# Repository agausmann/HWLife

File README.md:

# HWLife

Experiments in implementing Conway's Game of Life using tiled hardware.

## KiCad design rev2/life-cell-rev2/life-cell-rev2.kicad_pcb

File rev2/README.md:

# (WIP) HWLife Rev2

**This revision is on indefinite hold; I am currently working on a design
with independent modules and no backplane (rev3).**

A redesign of the backplane system.

Major changes:

- Module hardware
  - CH32V003
  - Right-angle backplane connectors and LEDs (allowing single-sided SMT assembly)
  - RGB LEDs (WS2812)

- Comms
  - Analog neighbor communication
  - Serial communication to individual modules (for programming state or dimming)

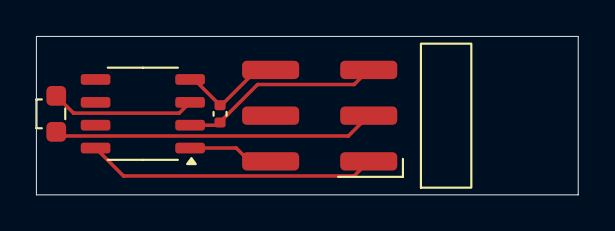
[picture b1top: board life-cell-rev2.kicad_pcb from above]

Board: 2 copper layers, 30.1 x 8.8 mm, 4 parts (0 on the bottom side), 6 nets.

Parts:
C1: 100nF; C_0402_1005Metric
D1: LED; LiteOn_LTST-S270KxKT
J1: Backplane; Conn_HCTL_PZ254-2-03-WS
U1: CH32V003J4M6; SOP-8_3.9x4.9mm_P1.27mm

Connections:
/DIM: D1.1 (K), J1.3
/LED: D1.2 (A), U1.3 (PA2)
/RX: J1.2, U1.1 (PD6/PA1)
/TX/SWIO: J1.1, U1.8 (PD1/PD4/PD5)
VDD: C1.1, J1.6, U1.4 (VDD)
VSS: C1.2, J1.5, U1.2 (VSS)

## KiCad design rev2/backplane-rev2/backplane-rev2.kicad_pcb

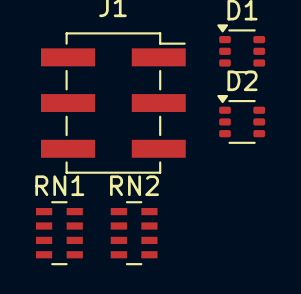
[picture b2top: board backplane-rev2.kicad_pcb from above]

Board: 2 copper layers, 5 parts (0 on the bottom side), 9 nets, no tracks yet.

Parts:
D1, D2: BAT54ADW; SOT-363_SC-70-6
J1: Module; PinSocket_2x03_P2.54mm_Vertical_SMD
RN1, RN2: 10K; R_Array_Concave_4x0603

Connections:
/A1/D: D1.3 (A), D1.6 (A), D2.3 (A), D2.6 (A), J1.3
unnamed: D1.1 (K), RN1.5 (R4.2)
unnamed: D1.2 (K), RN1.6 (R3.2)
unnamed: D1.4 (K), RN1.7 (R2.2)
unnamed: D1.5 (K), RN1.8 (R1.2)
unnamed: D2.1 (K), RN2.5 (R4.2)
unnamed: D2.2 (K), RN2.6 (R3.2)
unnamed: D2.4 (K), RN2.7 (R2.2)
unnamed: D2.5 (K), RN2.8 (R1.2)

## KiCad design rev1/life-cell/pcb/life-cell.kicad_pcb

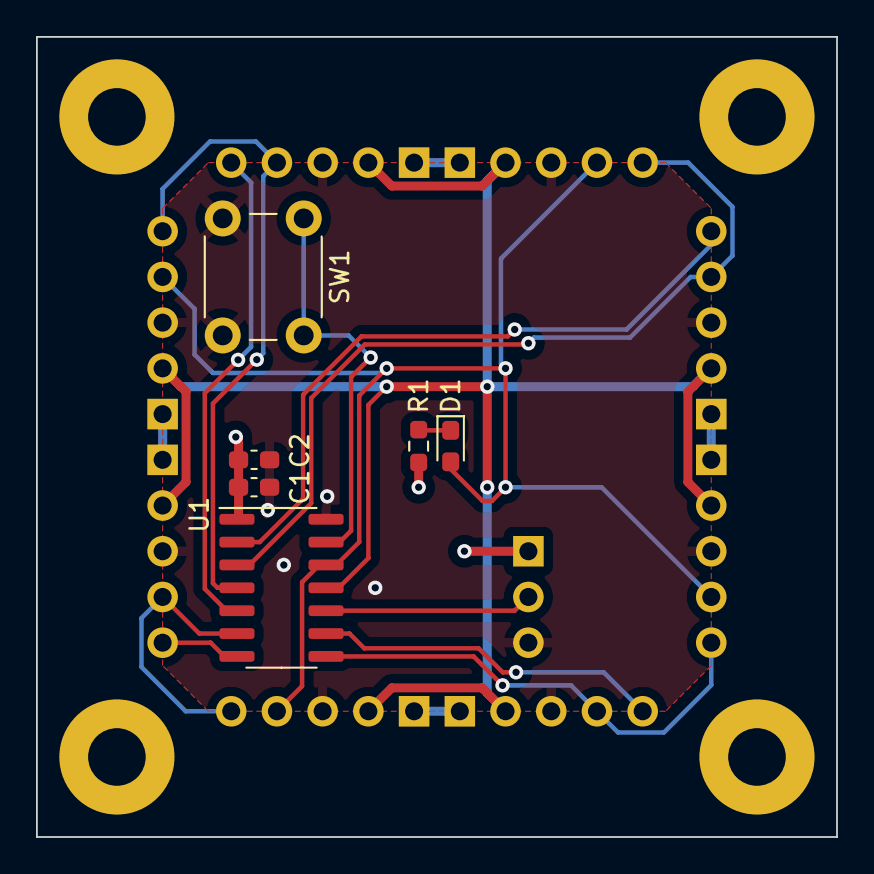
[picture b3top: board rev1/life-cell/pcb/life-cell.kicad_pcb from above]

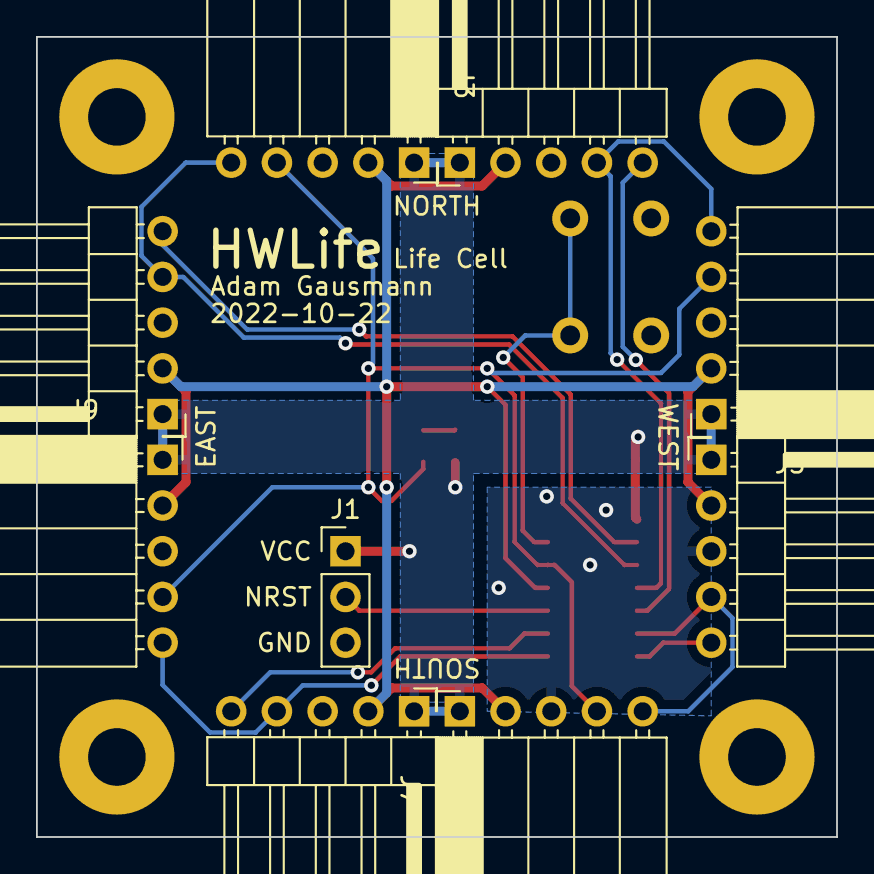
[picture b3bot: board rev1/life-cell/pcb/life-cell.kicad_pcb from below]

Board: 2 copper layers, 44.4 x 44.4 mm, 19 parts (9 on the bottom side), 15 nets.

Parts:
C1: 100nF; C_0603_1608Metric_Pad1.08x0.95mm_HandSolder
C2: Bulk; C_0603_1608Metric_Pad1.08x0.95mm_HandSolder
D1: LED; LED_0603_1608Metric_Pad1.05x0.95mm_HandSolder
H1, H2, H3, H4: M3; MountingHole_3.2mm_M3_Pad
J1: UPDI; PinHeader_1x03_P2.54mm_Vertical
J2, J4, J6, J8: Interconnect In; PinHeader_1x05_P2.54mm_Horizontal
J3, J5, J7, J9: Interconnect Out; PinSocket_1x05_P2.54mm_Horizontal
R1: 120R; R_0603_1608Metric_Pad0.98x0.95mm_HandSolder
SW1: Toggle; SW_PUSH_6mm_H4.3mm
U1: ATtiny404-SS; SOIC-14_3.9x8.7mm_P1.27mm

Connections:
/Cell/ADJ1: J2.4, J5.5, U1.4 (PA6)
/Cell/ADJ2: J3.5, J8.4, U1.3 (PA5)
/Cell/ADJ3: J6.4, J9.5, U1.8 (PB1)
/Cell/ADJ4: J4.4, J7.5, U1.6 (PB3)
/Cell/CLK: J2.2, J3.2, J4.2, J5.2, J6.2, J7.2, J8.2, J9.2, U1.11 (PA1)
/Cell/DIA1: J2.5, U1.5 (PA7)
/Cell/DIA2: J8.5, U1.2 (PA4)
/Cell/DIA3: J6.5, U1.9 (PB0)
/Cell/DIA4: J4.5, U1.7 (PB2)
/Cell/NRST: J1.2, U1.10 (~RESET/PA0)
/Cell/STATE: D1.2 (A), J3.4, J5.4, J7.4, J9.4, U1.12 (PA2)
/Cell/TOGGLE: SW1.1, U1.13 (PA3)
GND: C1.2, C2.2, J1.3, J2.3, J3.3, J4.3, J5.3, J6.3, J7.3, J8.3, J9.3, SW1.2, U1.14 (GND)
unnamed: D1.1 (K), R1.2
VCC: C1.1, C2.1, J1.1, J2.1, J3.1, J4.1, J5.1, J6.1, J7.1, J8.1, J9.1, R1.1, U1.1 (VCC)

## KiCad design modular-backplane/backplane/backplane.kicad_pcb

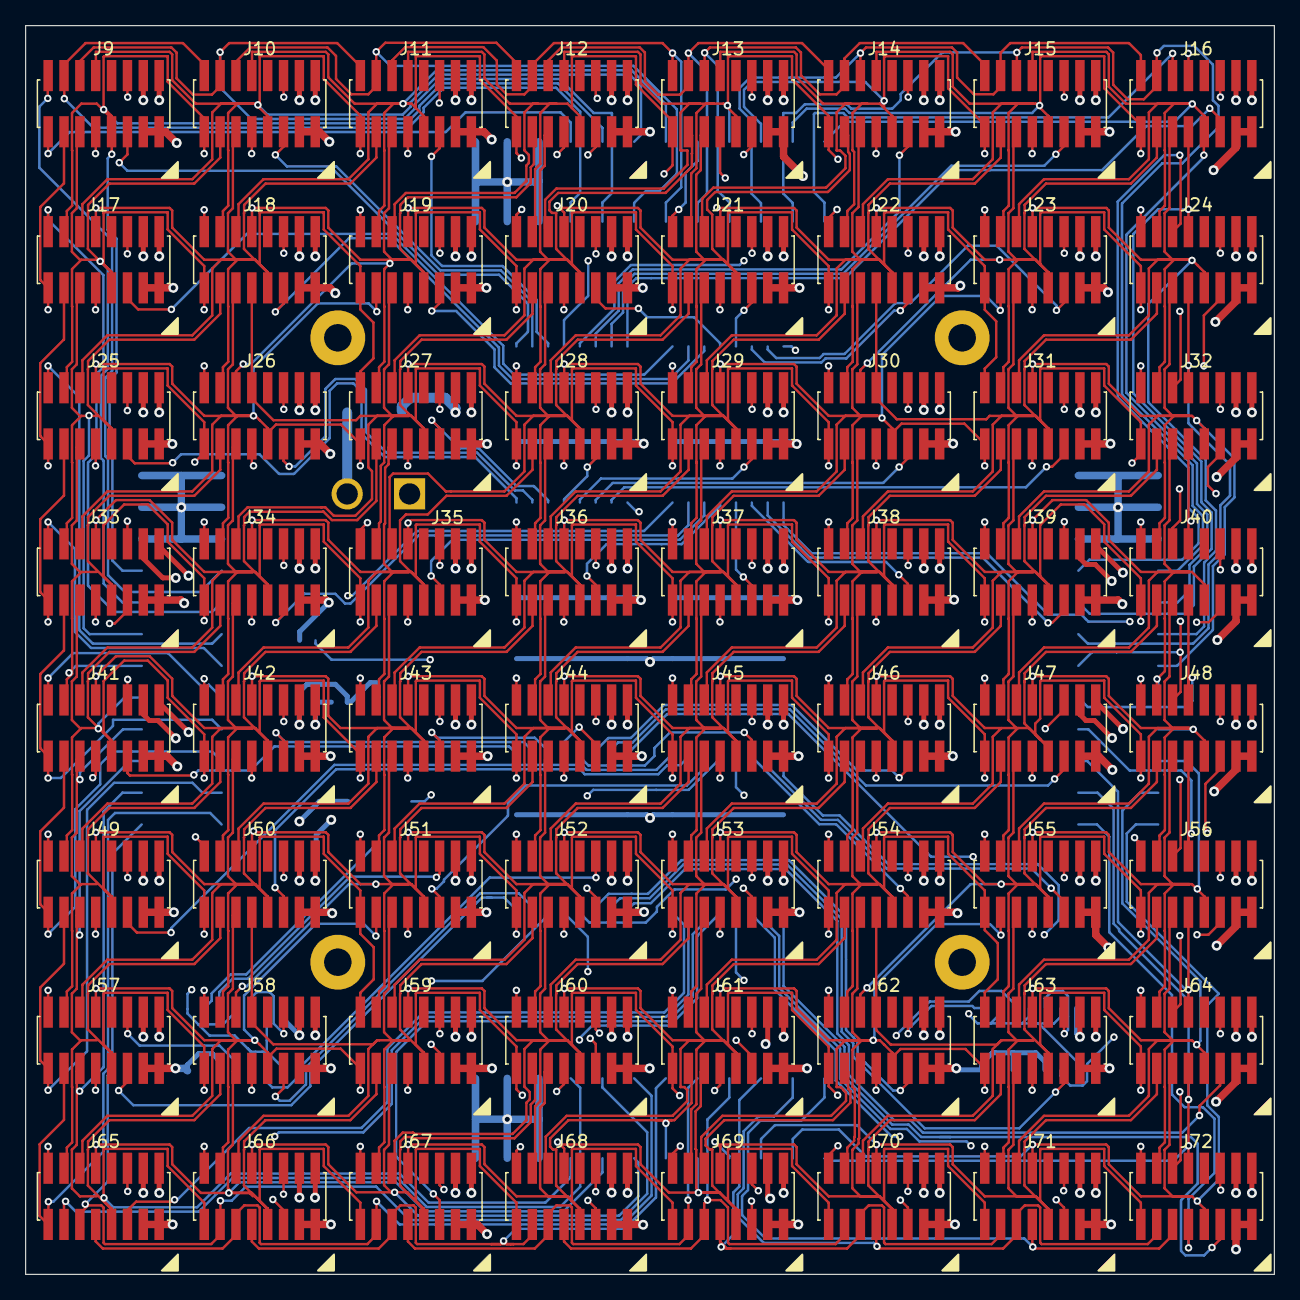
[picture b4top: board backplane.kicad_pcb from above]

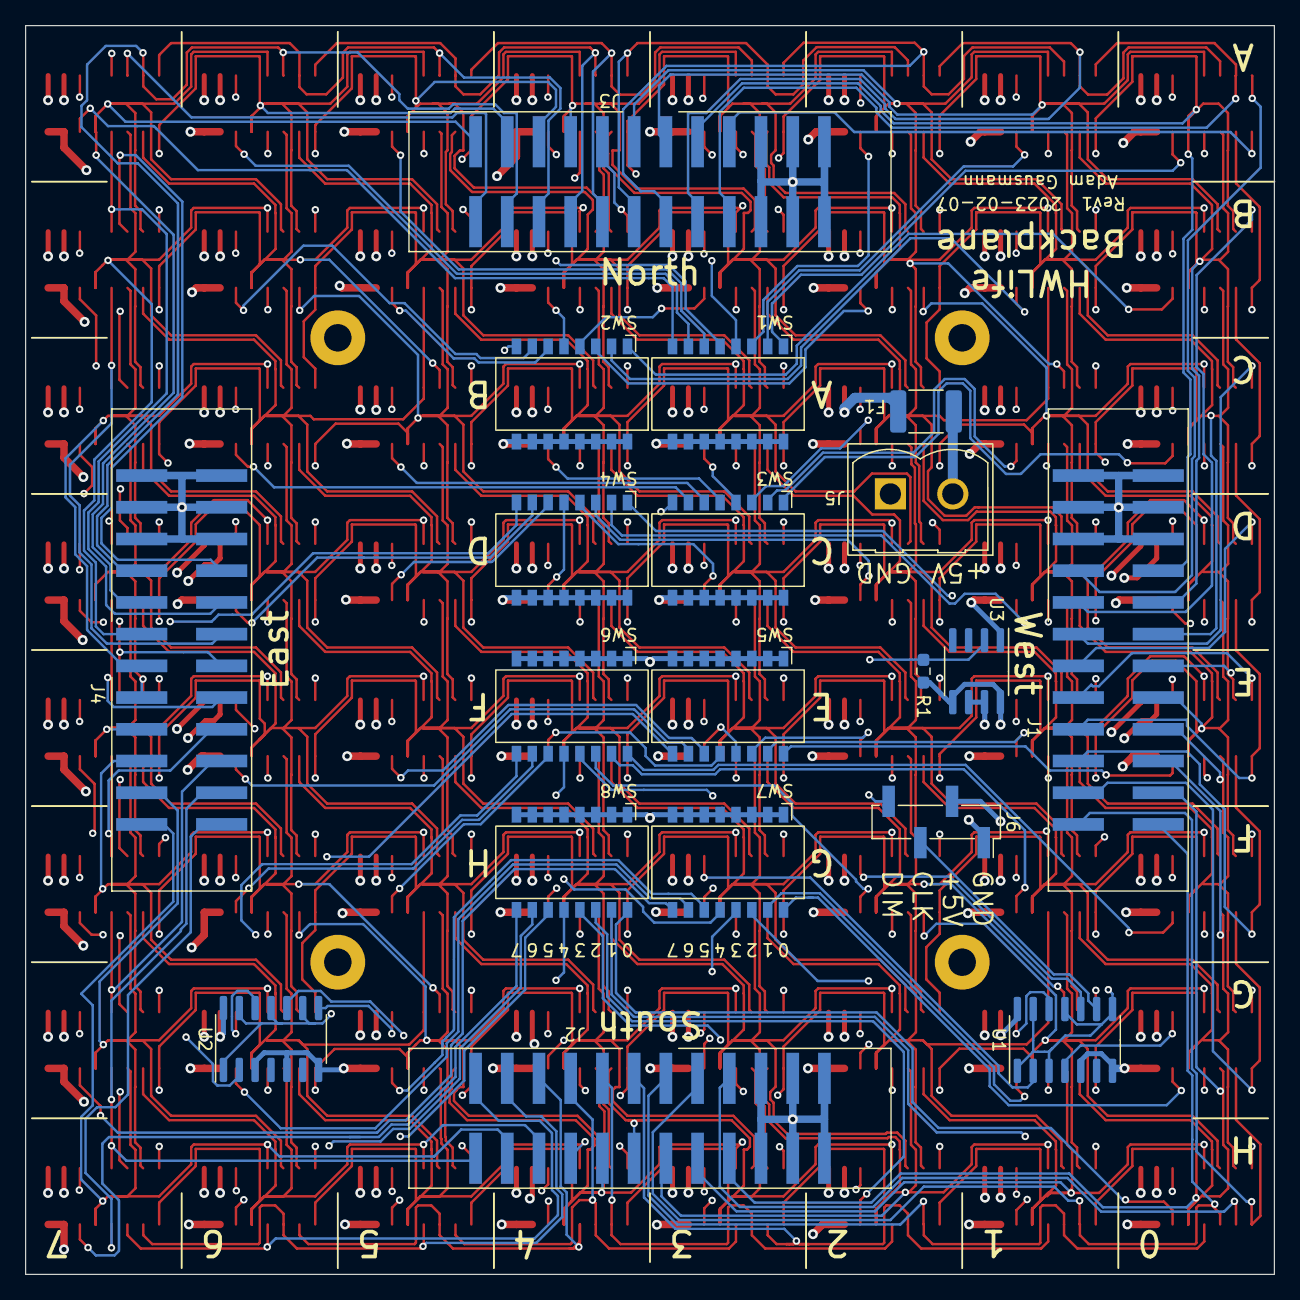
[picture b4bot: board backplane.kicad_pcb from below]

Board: 4 copper layers, 100.0 x 100.0 mm, 87 parts (19 on the bottom side), 179 nets.

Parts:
F1: 6V 3A; Fuse_1812_4532Metric_Pad1.30x3.40mm_HandSolder
H1, H2, H3, H4: MountingHole; MountingHole_2.2mm_M2_Pad
J1: West; JILN_321024M_02x12_P2.54mm_Vertical
J2: South; JILN_321024M_02x12_P2.54mm_Vertical
J3: North; JILN_321024M_02x12_P2.54mm_Vertical
J4: East; JILN_321024M_02x12_P2.54mm_Vertical
J5: 25-E900-02; Conn_NTE_25-E900-02_01x02_P5.00mm_Vertical
J6: MGMT; PinHeader_1x04_P2.54mm_Vertical_SMD_Pin1Right
J9, J10, J11, J12, J13, J14, J15, J16, J17, J18, J19, J20, J21, J22, J23, J24, J25, J26, J27, J28, J29, J30, J31, J32, J33, J34, J35, J36, J37, J38, J39, J40, J41, J42, J43, J44, J45, J46, J47, J48, J49, J50, J51, J52, J53, J54, J55, J56, J57, J58, J59, J60, J61, J62, J63, J64, J65, J66, J67, J68, J69, J70, J71, J72: Module; DEALON_DZ127S-22-16-55_02x08_P1.27mm_Vertical
R1: 10k; R_0603_1608Metric_Pad0.98x0.95mm_HandSolder
SW1: A; SW_DIP_SPSTx08_Slide_DEALON_SP-08P_P1.27mm
SW2: B; SW_DIP_SPSTx08_Slide_DEALON_SP-08P_P1.27mm
SW3: C; SW_DIP_SPSTx08_Slide_DEALON_SP-08P_P1.27mm
SW4: D; SW_DIP_SPSTx08_Slide_DEALON_SP-08P_P1.27mm
SW5: E; SW_DIP_SPSTx08_Slide_DEALON_SP-08P_P1.27mm
SW6: F; SW_DIP_SPSTx08_Slide_DEALON_SP-08P_P1.27mm
SW7: G; SW_DIP_SPSTx08_Slide_DEALON_SP-08P_P1.27mm
SW8: H; SW_DIP_SPSTx08_Slide_DEALON_SP-08P_P1.27mm
U1, U2: 74HC14; SOIC-14_3.9x8.7mm_P1.27mm
U3: VN5E160S; SOIC-8_3.9x4.9mm_P1.27mm

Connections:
+5V: F1.2, J6.2, J9.13, J10.13, J11.13, J12.13, J13.13, J14.13, J15.13, J16.13, J17.13, J18.13, J19.13, J20.13, J21.13, J22.13, J23.13, J24.13, J25.13, J26.13, J27.13, J28.13, J29.13, J30.13, J31.13, J32.13, J33.13, J34.13, J35.13, J36.13, J37.13, J38.13, J39.13, J40.13, J41.13, J42.13, J43.13, J44.13, J45.13, J46.13, J47.13, J48.13, J49.13, J50.13, J51.13, J52.13, J53.13, J54.13, J55.13, J56.13, J57.13, J58.13, J59.13, J60.13, J61.13, J62.13, J63.13, J64.13, J65.13, J66.13, J67.13, J68.13, J69.13, J70.13, J71.13, J72.13, R1.2, U1.14 (VCC), U2.14 (VCC), U3.5 (VCC), U3.8 (VCC)
/5V_IN: F1.1, J5.2
/CLK0: J9.11, J17.11, J25.11, J33.11, J41.11, J49.11, J57.11, J65.11, U1.4
/CLK1: J10.11, J18.11, J26.11, J34.11, J42.11, J50.11, J58.11, J66.11, U1.12
/CLK2: J11.11, J19.11, J27.11, J35.11, J43.11, J51.11, J59.11, J67.11, U1.10
/CLK3: J12.11, J20.11, J28.11, J36.11, J44.11, J52.11, J60.11, J68.11, U1.2
/CLK4: J13.11, J21.11, J29.11, J37.11, J45.11, J53.11, J61.11, J69.11, U2.10
/CLK5: J14.11, J22.11, J30.11, J38.11, J46.11, J54.11, J62.11, J70.11, U2.8
/CLK6: J15.11, J23.11, J31.11, J39.11, J47.11, J55.11, J63.11, J71.11, U2.12
/CLK7: J16.11, J24.11, J32.11, J40.11, J48.11, J56.11, J64.11, J72.11, U2.2
/Cell-A0/IN0: J3.8, J9.3, J10.1
/Cell-A0/IN1: J3.10, J9.5, J10.3, J11.1
/Cell-A0/IN5: J1.11, J9.4, J17.2, J25.1
/Cell-A0/IN6: J1.9, J3.7, J9.2, J17.1
/Cell-A0/IN7: J1.7, J9.1
/Cell-A0/STATE: J1.8, J3.9, J9.10, J10.2, J17.3, J18.1
/Cell-A1/IN1: J3.12, J10.5, J11.3, J12.1
/Cell-A1/STATE: J3.11, J9.7, J10.10, J11.2, J17.5, J18.3, J19.1
/Cell-A2/IN1: J3.14, J11.5, J12.3, J13.1
/Cell-A2/STATE: J3.13, J10.7, J11.10, J12.2, J18.5, J19.3, J20.1
/Cell-A3/IN1: J3.16, J12.5, J13.3, J14.1
/Cell-A3/STATE: J3.15, J11.7, J12.10, J13.2, J19.5, J20.3, J21.1
/Cell-A4/IN1: J3.18, J13.5, J14.3, J15.1
/Cell-A4/STATE: J3.17, J12.7, J13.10, J14.2, J20.5, J21.3, J22.1
/Cell-A5/IN1: J3.20, J14.5, J15.3, J16.1
/Cell-A5/STATE: J3.19, J13.7, J14.10, J15.2, J21.5, J22.3, J23.1
/Cell-A6/IN1: J3.22, J4.7, J15.5, J16.3
/Cell-A6/STATE: J3.21, J14.7, J15.10, J16.2, J22.5, J23.3, J24.1
/Cell-A7/IN1: J3.24, J16.5
/Cell-A7/IN2: J4.8, J16.7, J24.5
/Cell-A7/IN3: J4.10, J16.8, J24.7, J32.5
/Cell-A7/STATE: J3.23, J4.9, J15.7, J16.10, J23.5, J24.3
/Cell-B0/IN5: J1.13, J17.4, J25.2, J33.1
/Cell-B0/STATE: J1.10, J9.6, J10.4, J17.10, J18.2, J25.3, J26.1
/Cell-B1/STATE: J9.8, J10.6, J11.4, J17.7, J18.10, J19.2, J25.5, J26.3, J27.1
/Cell-B2/STATE: J10.8, J11.6, J12.4, J18.7, J19.10, J20.2, J26.5, J27.3, J28.1
/Cell-B3/STATE: J11.8, J12.6, J13.4, J19.7, J20.10, J21.2, J27.5, J28.3, J29.1
/Cell-B4/STATE: J12.8, J13.6, J14.4, J20.7, J21.10, J22.2, J28.5, J29.3, J30.1
/Cell-B5/STATE: J13.8, J14.6, J15.4, J21.7, J22.10, J23.2, J29.5, J30.3, J31.1
/Cell-B6/STATE: J14.8, J15.6, J16.4, J22.7, J23.10, J24.2, J30.5, J31.3, J32.1
/Cell-B7/IN3: J4.12, J24.8, J32.7, J40.5
/Cell-B7/STATE: J4.11, J15.8, J16.6, J23.7, J24.10, J31.5, J32.3
/Cell-C0/IN5: J1.15, J25.4, J33.2, J41.1
/Cell-C0/STATE: J1.12, J17.6, J18.4, J25.10, J26.2, J33.3, J34.1
/Cell-C1/STATE: J17.8, J18.6, J19.4, J25.7, J26.10, J27.2, J33.5, J34.3, J35.1
/Cell-C2/STATE: J18.8, J19.6, J20.4, J26.7, J27.10, J28.2, J34.5, J35.3, J36.1
/Cell-C3/STATE: J19.8, J20.6, J21.4, J27.7, J28.10, J29.2, J35.5, J36.3, J37.1
/Cell-C4/STATE: J20.8, J21.6, J22.4, J28.7, J29.10, J30.2, J36.5, J37.3, J38.1
/Cell-C5/STATE: J21.8, J22.6, J23.4, J29.7, J30.10, J31.2, J37.5, J38.3, J39.1
/Cell-C6/STATE: J22.8, J23.6, J24.4, J30.7, J31.10, J32.2, J38.5, J39.3, J40.1
/Cell-C7/IN3: J4.14, J32.8, J40.7, J48.5
/Cell-C7/STATE: J4.13, J23.8, J24.6, J31.7, J32.10, J39.5, J40.3
/Cell-D0/IN5: J1.17, J33.4, J41.2, J49.1
/Cell-D0/STATE: J1.14, J25.6, J26.4, J33.10, J34.2, J41.3, J42.1
/Cell-D1/STATE: J25.8, J26.6, J27.4, J33.7, J34.10, J35.2, J41.5, J42.3, J43.1
/Cell-D2/STATE: J26.8, J27.6, J28.4, J34.7, J35.10, J36.2, J42.5, J43.3, J44.1
/Cell-D3/STATE: J27.8, J28.6, J29.4, J35.7, J36.10, J37.2, J43.5, J44.3, J45.1
/Cell-D4/STATE: J28.8, J29.6, J30.4, J36.7, J37.10, J38.2, J44.5, J45.3, J46.1
/Cell-D5/STATE: J29.8, J30.6, J31.4, J37.7, J38.10, J39.2, J45.5, J46.3, J47.1
/Cell-D6/STATE: J30.8, J31.6, J32.4, J38.7, J39.10, J40.2, J46.5, J47.3, J48.1
/Cell-D7/IN3: J4.16, J40.8, J48.7, J56.5
/Cell-D7/STATE: J4.15, J31.8, J32.6, J39.7, J40.10, J47.5, J48.3
/Cell-E0/IN5: J1.19, J41.4, J49.2, J57.1
/Cell-E0/STATE: J1.16, J33.6, J34.4, J41.10, J42.2, J49.3, J50.1
/Cell-E1/STATE: J33.8, J34.6, J35.4, J41.7, J42.10, J43.2, J49.5, J50.3, J51.1
/Cell-E2/STATE: J34.8, J35.6, J36.4, J42.7, J43.10, J44.2, J50.5, J51.3, J52.1
/Cell-E3/STATE: J35.8, J36.6, J37.4, J43.7, J44.10, J45.2, J51.5, J52.3, J53.1
/Cell-E4/STATE: J36.8, J37.6, J38.4, J44.7, J45.10, J46.2, J52.5, J53.3, J54.1
/Cell-E5/STATE: J37.8, J38.6, J39.4, J45.7, J46.10, J47.2, J53.5, J54.3, J55.1
/Cell-E6/STATE: J38.8, J39.6, J40.4, J46.7, J47.10, J48.2, J54.5, J55.3, J56.1
/Cell-E7/IN3: J4.18, J48.8, J56.7, J64.5
/Cell-E7/STATE: J4.17, J39.8, J40.6, J47.7, J48.10, J55.5, J56.3
/Cell-F0/IN5: J1.21, J49.4, J57.2, J65.1
/Cell-F0/STATE: J1.18, J41.6, J42.4, J49.10, J50.2, J57.3, J58.1
/Cell-F1/STATE: J41.8, J42.6, J43.4, J49.7, J50.10, J51.2, J57.5, J58.3, J59.1
/Cell-F2/STATE: J42.8, J43.6, J44.4, J50.7, J51.10, J52.2, J58.5, J59.3, J60.1
/Cell-F3/STATE: J43.8, J44.6, J45.4, J51.7, J52.10, J53.2, J59.5, J60.3, J61.1
/Cell-F4/STATE: J44.8, J45.6, J46.4, J52.7, J53.10, J54.2, J60.5, J61.3, J62.1
/Cell-F5/STATE: J45.8, J46.6, J47.4, J53.7, J54.10, J55.2, J61.5, J62.3, J63.1
/Cell-F6/STATE: J46.8, J47.6, J48.4, J54.7, J55.10, J56.2, J62.5, J63.3, J64.1
/Cell-F7/IN3: J4.20, J56.8, J64.7, J72.5
/Cell-F7/STATE: J4.19, J47.8, J48.6, J55.7, J56.10, J63.5, J64.3
/Cell-G0/IN5: J1.23, J57.4, J65.2
/Cell-G0/STATE: J1.20, J49.6, J50.4, J57.10, J58.2, J65.3, J66.1
/Cell-G1/STATE: J49.8, J50.6, J51.4, J57.7, J58.10, J59.2, J65.5, J66.3, J67.1
/Cell-G2/STATE: J50.8, J51.6, J52.4, J58.7, J59.10, J60.2, J66.5, J67.3, J68.1
/Cell-G3/STATE: J51.8, J52.6, J53.4, J59.7, J60.10, J61.2, J67.5, J68.3, J69.1
/Cell-G4/STATE: J52.8, J53.6, J54.4, J60.7, J61.10, J62.2, J68.5, J69.3, J70.1
/Cell-G5/STATE: J53.8, J54.6, J55.4, J61.7, J62.10, J63.2, J69.5, J70.3, J71.1
/Cell-G6/STATE: J54.8, J55.6, J56.4, J62.7, J63.10, J64.2, J70.5, J71.3, J72.1
/Cell-G7/IN3: J2.24, J4.22, J64.8, J72.7
/Cell-G7/STATE: J4.21, J55.8, J56.6, J63.7, J64.10, J71.5, J72.3
/Cell-H0/IN3: J2.11, J65.8, J66.6, J67.4
/Cell-H0/IN4: J1.24, J2.9, J65.6, J66.4
/Cell-H0/IN5: J2.7, J65.4
/Cell-H0/STATE: J1.22, J2.8, J57.6, J58.4, J65.10, J66.2
/Cell-H1/IN3: J2.13, J66.8, J67.6, J68.4
/Cell-H1/STATE: J2.10, J57.8, J58.6, J59.4, J65.7, J66.10, J67.2
/Cell-H2/IN3: J2.15, J67.8, J68.6, J69.4
/Cell-H2/STATE: J2.12, J58.8, J59.6, J60.4, J66.7, J67.10, J68.2
/Cell-H3/IN3: J2.17, J68.8, J69.6, J70.4
/Cell-H3/STATE: J2.14, J59.8, J60.6, J61.4, J67.7, J68.10, J69.2
/Cell-H4/IN3: J2.19, J69.8, J70.6, J71.4
/Cell-H4/STATE: J2.16, J60.8, J61.6, J62.4, J68.7, J69.10, J70.2
/Cell-H5/IN3: J2.21, J70.8, J71.6, J72.4
/Cell-H5/STATE: J2.18, J61.8, J62.6, J63.4, J69.7, J70.10, J71.2
/Cell-H6/IN3: J2.23, J71.8, J72.6
/Cell-H6/STATE: J2.20, J62.8, J63.6, J64.4, J70.7, J71.10, J72.2
/Cell-H7/IN3: J4.24, J72.8
/Cell-H7/STATE: J2.22, J4.23, J63.8, J64.6, J71.7, J72.10
/T-A0: J9.12, SW1.1
/T-A1: J10.12, SW1.2
/T-A2: J11.12, SW1.3
/T-A3: J12.12, SW1.4
/T-A4: J13.12, SW1.5
/T-A5: J14.12, SW1.6
/T-A6: J15.12, SW1.7
/T-A7: J16.12, SW1.8
/T-B0: J17.12, SW2.1
/T-B1: J18.12, SW2.2
/T-B2: J19.12, SW2.3
/T-B3: J20.12, SW2.4
/T-B4: J21.12, SW2.5
/T-B5: J22.12, SW2.6
/T-B6: J23.12, SW2.7
/T-B7: J24.12, SW2.8
/T-C0: J25.12, SW3.1
/T-C1: J26.12, SW3.2
/T-C2: J27.12, SW3.3
/T-C3: J28.12, SW3.4
/T-C4: J29.12, SW3.5
/T-C5: J30.12, SW3.6
/T-C6: J31.12, SW3.7
/T-C7: J32.12, SW3.8
/T-D0: J33.12, SW4.1
/T-D1: J34.12, SW4.2
/T-D2: J35.12, SW4.3
/T-D3: J36.12, SW4.4
/T-D4: J37.12, SW4.5
/T-D5: J38.12, SW4.6
/T-D6: J39.12, SW4.7
/T-D7: J40.12, SW4.8
/T-E0: J41.12, SW5.16
/T-E1: J42.12, SW5.15
/T-E2: J43.12, SW5.14
/T-E3: J44.12, SW5.13
/T-E4: J45.12, SW5.12
/T-E5: J46.12, SW5.11
/T-E6: J47.12, SW5.10
/T-E7: J48.12, SW5.9
/T-F0: J49.12, SW6.16
/T-F1: J50.12, SW6.15
/T-F2: J51.12, SW6.14
/T-F3: J52.12, SW6.13
/T-F4: J53.12, SW6.12
/T-F5: J54.12, SW6.11
/T-F6: J55.12, SW6.10
/T-F7: J56.12, SW6.9
/T-G0: J57.12, SW7.16
/T-G1: J58.12, SW7.15
/T-G2: J59.12, SW7.14
/T-G3: J60.12, SW7.13
/T-G4: J61.12, SW7.12
/T-G5: J62.12, SW7.11
/T-G6: J63.12, SW7.10
/T-G7: J64.12, SW7.9
/T-H0: J65.12, SW8.16
/T-H1: J66.12, SW8.15
/T-H2: J67.12, SW8.14
/T-H3: J68.12, SW8.13
/T-H4: J69.12, SW8.12
/T-H5: J70.12, SW8.11
/T-H6: J71.12, SW8.10
/T-H7: J72.12, SW8.9
CLK: J6.3, U1.9
DIM: J6.4, R1.1, U3.2 (INPUT)
GND: J1.1, J1.2, J1.3, J1.4, J1.5, J1.6, J2.1, J2.2, J2.3, J2.4, J2.5, J2.6, J3.1, J3.2, J3.3, J3.4, J3.5, J3.6, J4.1, J4.2, J4.3, J4.4, J4.5, J4.6, J5.1, J6.1, J9.14, J9.16, J10.14, J10.16, J11.14, J11.16, J12.14, J12.16, J13.14, J13.16, J14.14, J14.16, J15.14, J15.16, J16.14, J16.16, J17.14, J17.16, J18.14, J18.16, J19.14, J19.16, J20.14, J20.16, J21.14, J21.16, J22.14, J22.16, J23.14, J23.16, J24.14, J24.16, J25.14, J25.16, J26.14, J26.16, J27.14, J27.16, J28.14, J28.16, J29.14, J29.16, J30.14, J30.16, J31.14, J31.16, J32.14, J32.16, J33.14, J33.16, J34.14, J34.16, J35.14, J35.16, J36.14, J36.16, J37.14, J37.16, J38.14, J38.16, J39.14, J39.16, J40.14, J40.16, J41.14, J41.16, J42.14, J42.16, J43.14, J43.16, J44.14, J44.16, J45.14, J45.16, J46.14, J46.16, J47.14, J47.16, J48.14, J48.16, J49.14, J49.16, J50.14, J50.16, J51.14, J51.16, J52.14, J52.16, J53.14, J53.16, J54.14, J54.16, J55.14, J55.16, J56.14, J56.16, J57.14, J57.16, J58.14, J58.16, J59.14, J59.16, J60.14, J60.16, J61.14, J61.16, J62.14, J62.16, J63.14, J63.16, J64.14, J64.16, J65.14, J65.16, J66.14, J66.16, J67.14, J67.16, J68.14, J68.16, J69.14, J69.16, J70.14, J70.16, J71.14, J71.16, J72.14, J72.16, SW1.9, SW1.10, SW1.11, SW1.12, SW1.13, SW1.14, SW1.15, SW1.16, SW2.9, SW2.10, SW2.11, SW2.12, SW2.13, SW2.14, SW2.15, SW2.16, SW3.9, SW3.10, SW3.11, SW3.12, SW3.13, SW3.14, SW3.15, SW3.16, SW4.9, SW4.10, SW4.11, SW4.12, SW4.13, SW4.14, SW4.15, SW4.16, SW5.1, SW5.2, SW5.3, SW5.4, SW5.5, SW5.6, SW5.7, SW5.8, SW6.1, SW6.2, SW6.3, SW6.4, SW6.5, SW6.6, SW6.7, SW6.8, SW7.1, SW7.2, SW7.3, SW7.4, SW7.5, SW7.6, SW7.7, SW7.8, SW8.1, SW8.2, SW8.3, SW8.4, SW8.5, SW8.6, SW8.7, SW8.8, U1.5, U1.7 (GND), U2.3, U2.5, U2.7 (GND), U3.1 (GND)
unnamed: U1.1, U1.3, U1.8, U1.11, U1.13, U2.1, U2.9, U2.11, U2.13
VLED: J9.15, J10.15, J11.15, J12.15, J13.15, J14.15, J15.15, J16.15, J17.15, J18.15, J19.15, J20.15, J21.15, J22.15, J23.15, J24.15, J25.15, J26.15, J27.15, J28.15, J29.15, J30.15, J31.15, J32.15, J33.15, J34.15, J35.15, J36.15, J37.15, J38.15, J39.15, J40.15, J41.15, J42.15, J43.15, J44.15, J45.15, J46.15, J47.15, J48.15, J49.15, J50.15, J51.15, J52.15, J53.15, J54.15, J55.15, J56.15, J57.15, J58.15, J59.15, J60.15, J61.15, J62.15, J63.15, J64.15, J65.15, J66.15, J67.15, J68.15, J69.15, J70.15, J71.15, J72.15, U3.6 (OUTPUT), U3.7 (OUTPUT)

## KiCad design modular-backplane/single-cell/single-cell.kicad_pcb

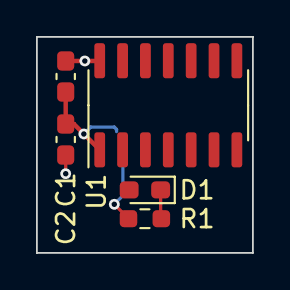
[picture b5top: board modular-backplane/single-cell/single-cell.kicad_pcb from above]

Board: 2 copper layers, 12.0 x 12.0 mm, 6 parts (1 on the bottom side), 7 nets.

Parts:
C1: 100nF; C_0603_1608Metric_Pad1.08x0.95mm_HandSolder
C2: Bulk; C_0603_1608Metric_Pad1.08x0.95mm_HandSolder
D1: LED; LED_0603_1608Metric_Pad1.05x0.95mm_HandSolder
J1: To Backplane; Molex_SlimStack_216701-0209_02x10_P0.35mm_Vertical
R1: 120R; R_0603_1608Metric_Pad0.98x0.95mm_HandSolder
U1: ATtiny404-SS; SOIC-14_3.9x8.7mm_P1.27mm

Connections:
/NRST: J1.15, U1.10 (~RESET/PA0)
/STATE: D1.2 (A), J1.14, U1.3 (PA5)
/TOGGLE: J1.16, U1.2 (PA4)
/VLED: J1.18, R1.1
GND: C1.2, C2.2, J1.20, U1.14 (GND)
unnamed: D1.1 (K), R1.2
VCC: C1.1, C2.1, J1.19, U1.1 (VCC)

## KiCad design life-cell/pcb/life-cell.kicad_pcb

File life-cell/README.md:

# Life Cell

A tileable Life processor, implementing a single cell per tile.

## Future improvements

- Current connectors are bulky, size could be reduced significantly if I use
more low-profile ones.

- Connector pinouts are rotationally symmetric, so board orientation doesn't matter. However, this is limited by having gendered connectors. Hermaphroditic connectors would be cool but more expensive...

- Cost efficiency ($ per cell) of this design is not optimal. Alternative
design possibilities:

  - Backplane design for distributing power and clock and routing states between
  neighbors, modules only contain logic and state. This would reduce the
  connector size, number of connectors, and size/complexity of modules.

  - Combining multiple cells into a single module. The MCU is one of the main
  factors in the overall cost per cell, so the goal would be to maximize the
  utilization of the MCU by increasing the number of cells it processes per
  generation.

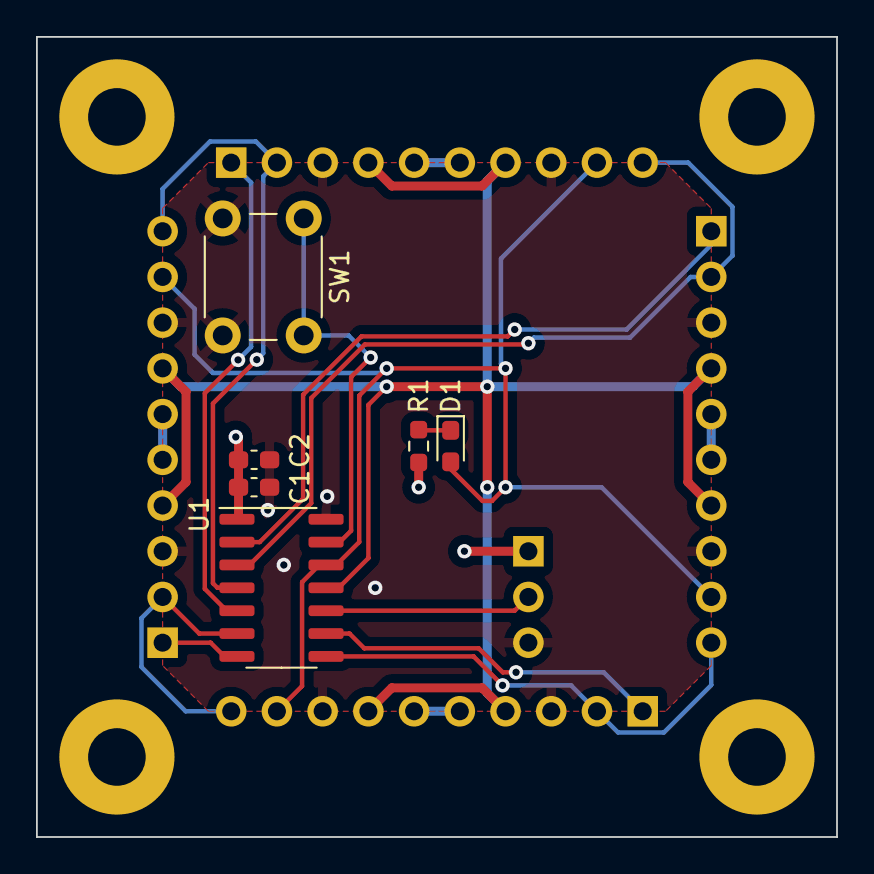
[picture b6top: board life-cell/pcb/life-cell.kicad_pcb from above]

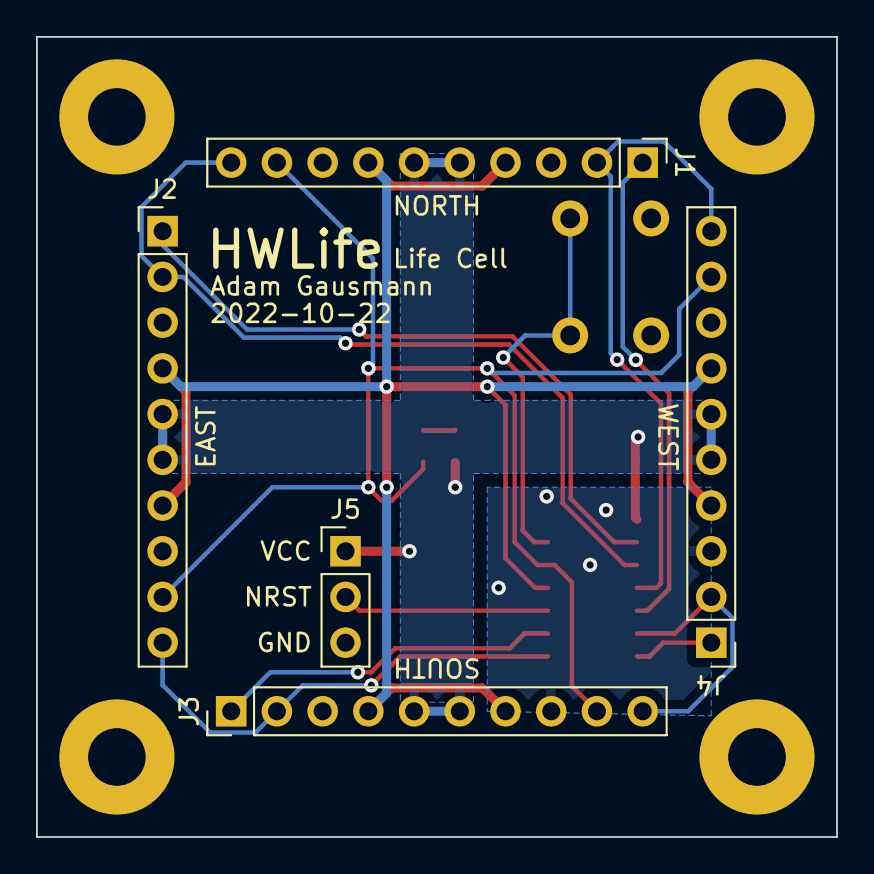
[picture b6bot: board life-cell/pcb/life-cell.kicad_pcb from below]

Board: 2 copper layers, 44.4 x 44.4 mm, 15 parts (5 on the bottom side), 15 nets.

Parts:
C1: 100nF; C_0603_1608Metric_Pad1.08x0.95mm_HandSolder
C2: Bulk; C_0603_1608Metric_Pad1.08x0.95mm_HandSolder
D1: LED; LED_0603_1608Metric_Pad1.05x0.95mm_HandSolder
H1, H2, H3, H4: M3; MountingHole_3.2mm_M3_Pad
J1, J2, J3, J4: Interconnect; PinHeader_1x10_P2.54mm_Vertical
J5: UPDI; PinHeader_1x03_P2.54mm_Vertical
R1: 120R; R_0603_1608Metric_Pad0.98x0.95mm_HandSolder
SW1: Toggle; SW_PUSH_6mm_H4.3mm
U1: ATtiny404-SS; SOIC-14_3.9x8.7mm_P1.27mm

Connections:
/Cell/ADJ1: J1.2, J4.10, U1.4 (PA6)
/Cell/ADJ2: J1.10, J2.2, U1.3 (PA5)
/Cell/ADJ3: J2.10, J3.2, U1.8 (PB1)
/Cell/ADJ4: J3.10, J4.2, U1.6 (PB3)
/Cell/CLK: J1.4, J1.7, J2.4, J2.7, J3.4, J3.7, J4.4, J4.7, U1.11 (PA1)
/Cell/DIA1: J1.1, U1.5 (PA7)
/Cell/DIA2: J2.1, U1.2 (PA4)
/Cell/DIA3: J3.1, U1.9 (PB0)
/Cell/DIA4: J4.1, U1.7 (PB2)
/Cell/NRST: J5.2, U1.10 (~RESET/PA0)
/Cell/STATE: D1.2 (A), J1.9, J2.9, J3.9, J4.9, U1.12 (PA2)
/Cell/TOGGLE: SW1.1, U1.13 (PA3)
GND: C1.2, C2.2, J1.3, J1.8, J2.3, J2.8, J3.3, J3.8, J4.3, J4.8, J5.3, SW1.2, U1.14 (GND)
unnamed: D1.1 (K), R1.2
VCC: C1.1, C2.1, J1.5, J1.6, J2.5, J2.6, J3.5, J3.6, J4.5, J4.6, J5.1, R1.1, U1.1 (VCC)

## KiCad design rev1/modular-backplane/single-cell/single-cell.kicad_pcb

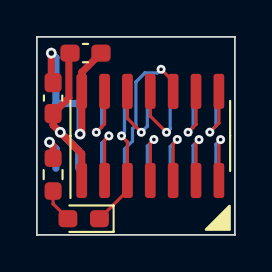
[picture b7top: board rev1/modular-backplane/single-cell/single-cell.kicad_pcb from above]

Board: 2 copper layers, 11.0 x 11.0 mm, 8 parts (1 on the bottom side), 16 nets.

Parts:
C1: 100nF; C_0603_1608Metric_Pad1.08x0.95mm_HandSolder
C2: Bulk; C_0603_1608Metric_Pad1.08x0.95mm_HandSolder
D1: LED; LED_0603_1608Metric_Pad1.05x0.95mm_HandSolder
H1, H2: Pull; Hole_Cell
J1: To Backplane; XKB_X1321FVS_02x08_P1.27mm_Vertical
R1: 120R; R_0603_1608Metric_Pad0.98x0.95mm_HandSolder
U1: ATtiny404-SS; SOIC-14_3.9x8.7mm_P1.27mm

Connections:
+5V: C1.1, C2.1, J1.13, U1.1 (VCC)
/CLK: J1.11, U1.2 (PA4)
/IN0: J1.3, U1.6 (PB3)
/IN1: J1.5, U1.5 (PA7)
/IN2: J1.7, U1.4 (PA6)
/IN3: J1.8, U1.12 (PA2)
/IN4: J1.6, U1.11 (PA1)
/IN5: J1.4, U1.9 (PB0)
/IN6: J1.2, U1.8 (PB1)
/IN7: J1.1, U1.7 (PB2)
/INIT: J1.12, U1.13 (PA3)
/NRST: J1.9, U1.10 (~RESET/PA0)
/STATE: D1.1 (K), J1.10, U1.3 (PA5)
/VLED: J1.15, R1.1
GND: C1.2, C2.2, J1.14, J1.16, U1.14 (GND)
unnamed: D1.2 (A), R1.2

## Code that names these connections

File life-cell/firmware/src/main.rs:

#![no_std]
#![no_main]

use avrxmega_hal::{
    pac::Peripherals,
    port::{
        mode::{Input, PullUp},
        Pin,
    },
    Pins,
};
use core::panic::PanicInfo;

const EEPROM_START: usize = 0x1f00;
const EEPROM_SIZE: usize = 128;

#[avrxmega_hal::entry]
fn main() -> ! {
    let dp = Peripherals::take().unwrap();
    let pins = Pins::new(dp.PORTA, dp.PORTB);

    let eeprom: &[u8; EEPROM_SIZE] = unsafe { &*(EEPROM_START as *const [u8; EEPROM_SIZE]) };

    // Order matters for the index calculation -
    // Starting top-left and going around clockwise:
    let neighbors: [Pin<Input<PullUp>>; 8] = [
        pins.pa7.into_pull_up_input().downgrade(), // DIA1
        pins.pa6.into_pull_up_input().downgrade(), // ADJ1
        pins.pa4.into_pull_up_input().downgrade(), // DIA2
        pins.pa5.into_pull_up_input().downgrade(), // ADJ2
        pins.pb0.into_pull_up_input().downgrade(), // DIA3
        pins.pb1.into_pull_up_input().downgrade(), // ADJ3
        pins.pb2.into_pull_up_input().downgrade(), // DIA4
        pins.pb3.into_pull_up_input().downgrade(), // ADJ4
    ];
    let clk = pins.pa1.into_pull_up_input();
    let mut state = pins.pa2.into_opendrain_high();
    let mut alive = false;
    loop {
        //TODO interrupt-based sleep/wake
        while clk.is_high() {}

        let mut alive_neighbors: u8 = 0;
        for neighbor in &neighbors {
            alive_neighbors <<= 1;
            alive_neighbors |= neighbor.is_low() as u8;
        }

        let index = usize::from_le_bytes([alive_neighbors, alive as u8]);

        while clk.is_low() {}

        let byte = index / 8;
        let bit = index % 8;
        alive = (eeprom[byte] & (1 << bit)) != 0;

        if alive {
            state.set_low();
        } else {
            state.set_high();
        }
    }
}

#[panic_handler]
fn panic(_info: &PanicInfo) -> ! {
    loop {}
}

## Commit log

2022-10-23 Initial commit with prototype Life Cell design
2022-10-24 Fix connector models, add renders and README
2022-10-24 Fix LED resistor value
2022-10-24 Add notoes about cost efficiency
2022-10-24 Backplane design would also reduce module size
2022-10-25 life-cell: Move PCB design files to a subdirectory
2022-10-25 life-cell Add skeleton project for firmware
2022-10-25 Add note about avr-device patch
2022-10-26 life-cell: Implement Life firmware
2022-10-26 Add design files for diffuse front cover
2022-10-26 Generalize firmware by computing an index into EEPROM.
    The index is calculated from the cell's own state and its neighbor states,
    which allows it to emulate any Life-like automaton and, more generally,
    any 2-state cellular automaton in which each cell's state is a function of its
    Moore neighborhood.
2022-10-27 Add EEPROM documentation and life image
2022-10-27 Add NSEW schem/silkscreen labels
2022-10-27 Add more details to docs
2022-10-28 Add example bits in a plaintext format
2023-01-07 life-cell: Change to sharp corners
2023-01-07 Update avr-hal
2023-01-13 Switch to "symmetric" connector layout.
    Each side has half male pins and half female pins, for a truly
    symmetric experience!
2023-01-19 Modular backplane initial design
    I should have committed several times earlier, but better late than
    never.
    New design concept: Individual cells are pluggable modules, and a
    tileable backplane board provides interconnect, power, and clock.
    Current status: Pretty much everything is designed;
    almost everything is routed.
2023-01-19 Update some component details
2023-01-20 Add more part details
2023-01-20 Place and route DIP switches
2023-01-21 Place and route power/management connectors and power switch
2023-01-22 Place and route clock tree; remove NRST from management header
2023-01-23 Backplane finishing touches
2023-02-07 Add PTC fuse; add orientation marks for modules
2023-02-07 (Re)route single-cell module; add grabbing holes and markings
2024-03-04 Move to rev1 subdir
2024-03-23 rev3 firmware skeleton
2024-03-23 rev1: commit blinky example
2024-03-23 rev1 misc 3d models
2024-03-23 rev2 archive
2024-03-24 Remove profiles from non-root crate
2024-03-25 Set up timers; PWM demo
2024-03-26 DMA-driven duty cycle demo
2024-03-27 Refactor for DMA interrupts, add data encoder
